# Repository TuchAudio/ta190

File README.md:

# ta190
Low Noise Moving-Coil Pre-Amplifier

## Purpose
Generic _standalone_ pre-preamp for **Moving Coil** phono cartridges, applying a fixed linear voltage gain.

## Design
The use of **four _common-base_ stages in parallel**  provides **low input impedance** (100 Ω) and **improved _signal-to-noise_ ratio** (by 6 dB).

## Specs
- **Power supply:** 9-12 V, asymmetrical (just a few mA)
- **Gain:** x33 (+34 dB)
- **Input Sensitivity:** 0.11 mV over 100 Ω (for a 3.6 mV output, suitable for [TuchAudio 103 preamp](../../../ta103))
- **Nominal Output level:** 3.6 mV over 110 kΩ (from a 0.11 mV input)
- **Output impedance:** 3.3 kΩ. _Lower load impedances are allowed, but diminished output level and impaired bass response are to be expected_.

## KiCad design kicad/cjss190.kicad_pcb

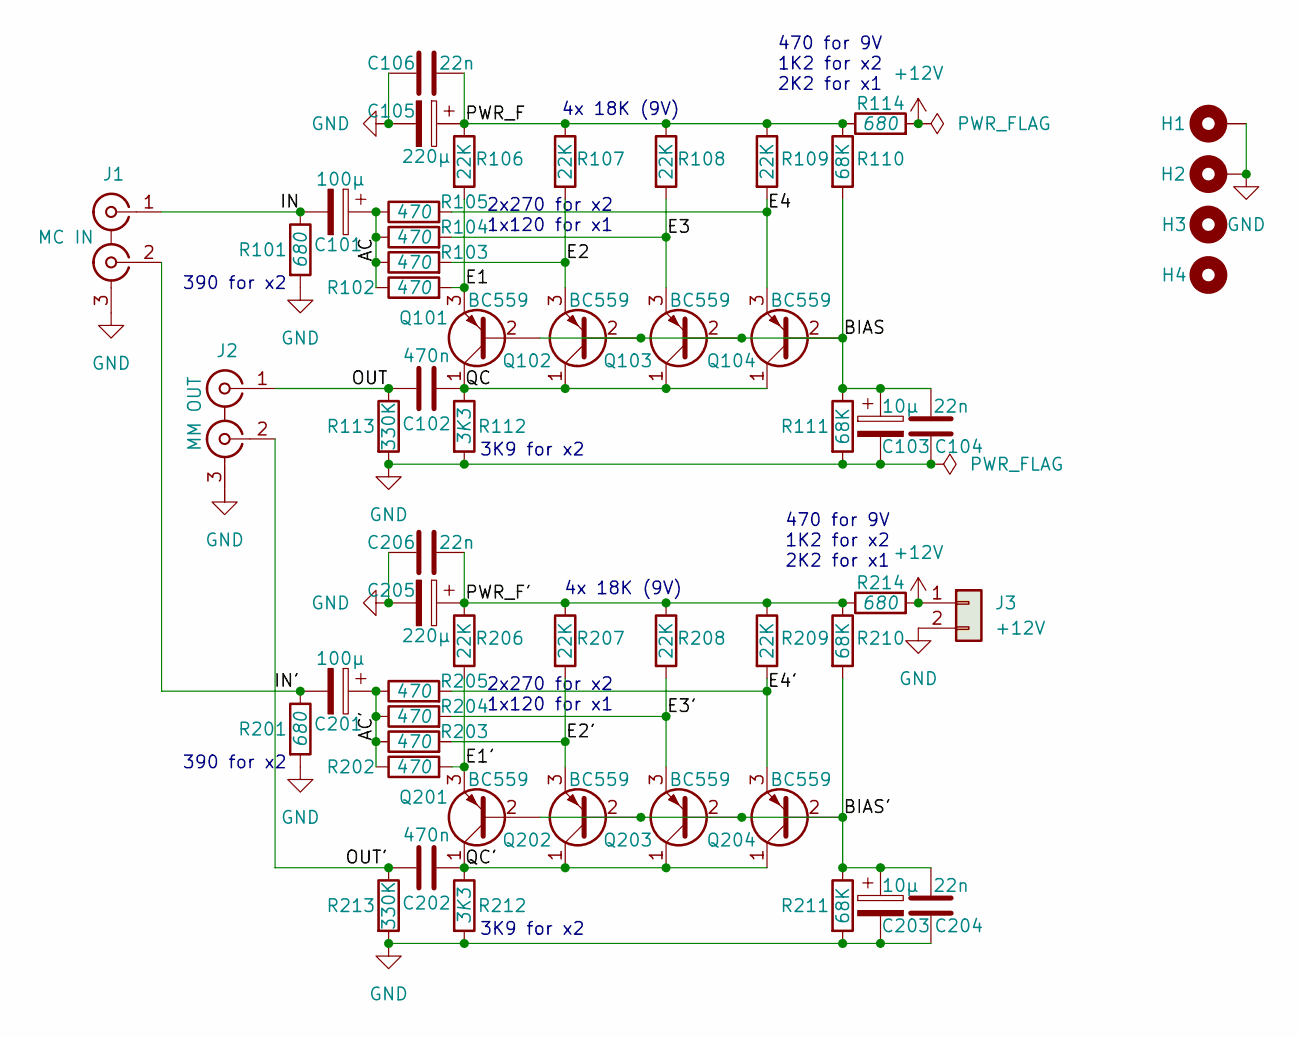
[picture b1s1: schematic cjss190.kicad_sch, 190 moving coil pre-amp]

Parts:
C101, C201: 100µ; CP_Radial_D4.0mm_P1.50mm
C102, C202: 470n; C_Rect_L7.2mm_W3.0mm_P5.00mm_FKS2_FKP2_MKS2_MKP2
C103, C203: 10µ; CP_Radial_D4.0mm_P1.50mm
C104, C106, C204, C206: 22n; C_Disc_D6.0mm_W2.5mm_P5.00mm
C105, C205: 220µ; CP_Radial_D6.3mm_P2.50mm
H1, H2: MountingHole_Pad; MountingHole_3.2mm_M3_DIN965_Pad
H3, H4: MountingHole; MountingHole_3.2mm_M3
J1: MC IN; 2xRCA_vertical
J2: MM OUT; 2xRCA_vertical
J3: +12V; PinSocket_1x02_P2.54mm_Vertical
Q101, Q102, Q103, Q104, Q201, Q202, Q203, Q204: BC559; TO-92_Inline
R101, R114, R201, R214: 680; R_Axial_DIN0207_L6.3mm_D2.5mm_P10.16mm_Horizontal
R102, R103, R104, R105, R202, R203, R204, R205: 470; R_Axial_DIN0207_L6.3mm_D2.5mm_P10.16mm_Horizontal
R106, R107, R108, R109, R206, R207, R208, R209: 22K; R_Axial_DIN0207_L6.3mm_D2.5mm_P10.16mm_Horizontal
R110, R111, R210, R211: 68K; R_Axial_DIN0207_L6.3mm_D2.5mm_P10.16mm_Horizontal
R112, R212: 3K3; R_Axial_DIN0207_L6.3mm_D2.5mm_P10.16mm_Horizontal
R113, R213: 330K; R_Axial_DIN0207_L6.3mm_D2.5mm_P10.16mm_Horizontal

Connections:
+12V: J3.1, R114.2, R214.2
/AC: C101.1, R102.1, R103.1, R104.1, R105.1
/AC': C201.1, R202.1, R203.1, R204.1, R205.1
/BIAS: C103.1, C104.1, Q101.2 (B), Q102.2 (B), Q103.2 (B), Q104.2 (B), R110.2, R111.1
/BIAS': C203.1, C204.1, Q201.2 (B), Q202.2 (B), Q203.2 (B), Q204.2 (B), R210.2, R211.1
/E1: Q101.3 (E), R102.2, R106.2
/E1': Q201.3 (E), R202.2, R206.2
/E2: Q102.3 (E), R103.2, R107.2
/E2': Q202.3 (E), R203.2, R207.2
/E3: Q103.3 (E), R104.2, R108.2
/E3': Q203.3 (E), R204.2, R208.2
/E4: Q104.3 (E), R105.2, R109.2
/E4': Q204.3 (E), R205.2, R209.2
/IN: C101.2, J1.1 (IN1), R101.1
/IN': C201.2, J1.2 (IN2), R201.1
/OUT: C102.1, J2.1 (IN1), R113.1
/OUT': C202.1, J2.2 (IN2), R213.1
/PWR_F: C105.1, C106.2, R106.1, R107.1, R108.1, R109.1, R110.1, R114.1
/PWR_F': C205.1, C206.2, R206.1, R207.1, R208.1, R209.1, R210.1, R214.1
/QC: C102.2, Q101.1 (C), Q102.1 (C), Q103.1 (C), Q104.1 (C), R112.1
/QC': C202.2, Q201.1 (C), Q202.1 (C), Q203.1 (C), Q204.1 (C), R212.1
GND: C103.2, C104.2, C105.2, C106.1, C203.2, C204.2, C205.2, C206.1, H1.1, H2.1, J1.3 (EXT), J2.3 (EXT), J3.2, R101.2, R111.2, R112.2, R113.2, R201.2, R211.2, R212.2, R213.2

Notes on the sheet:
470 for 9V 1K2 for x2 2K2 for x1
390 for x2
3K9 for x2
4x 18K (9V)
2x270 for x2 1x120 for x1

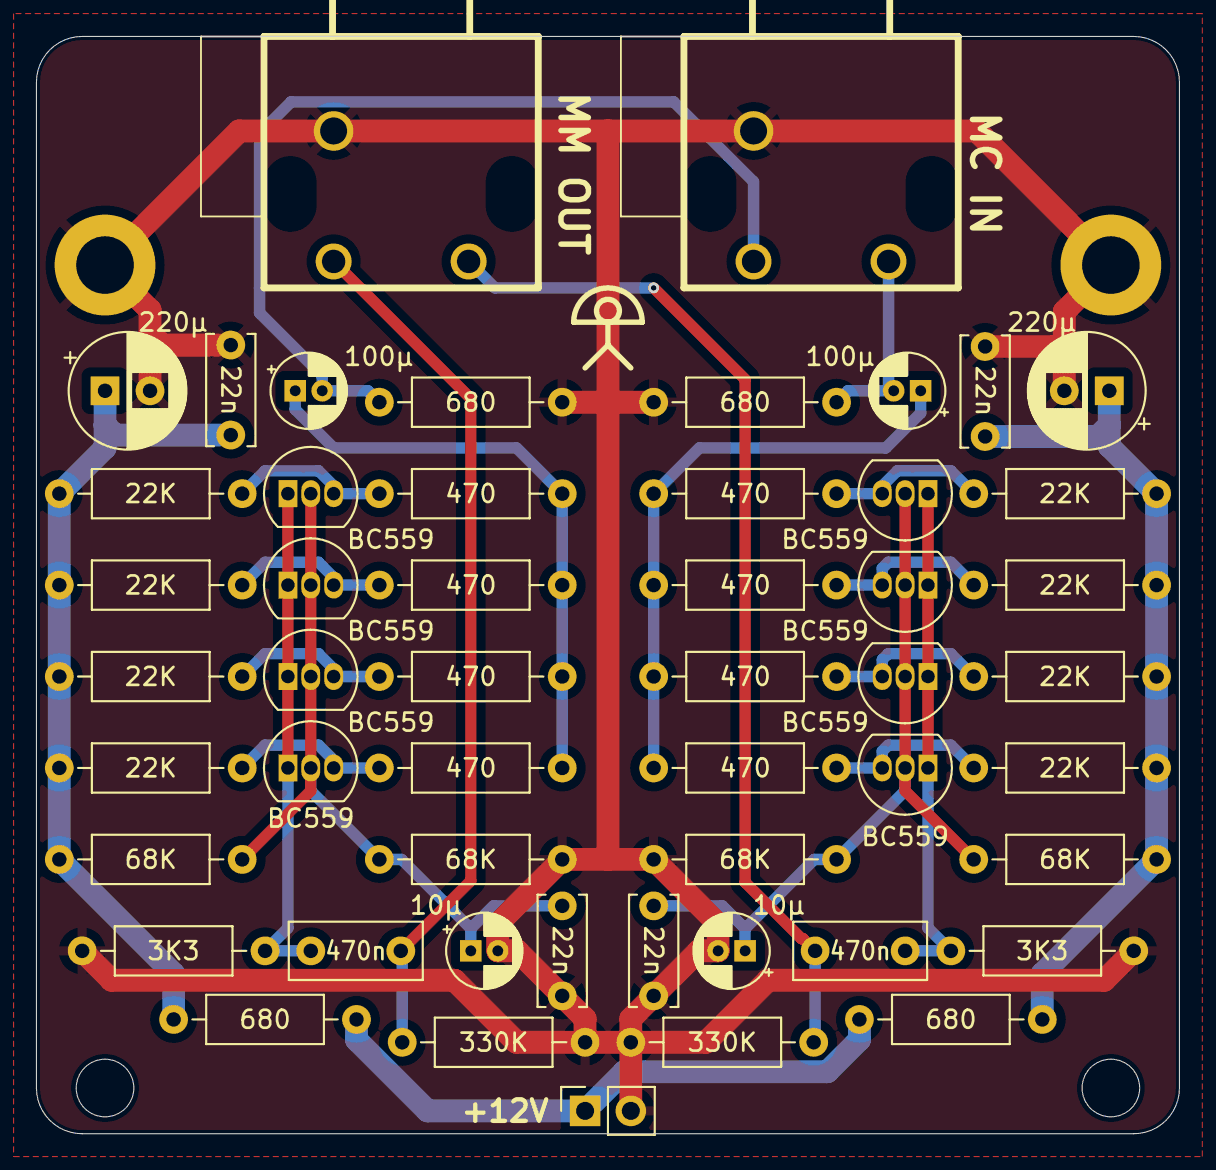
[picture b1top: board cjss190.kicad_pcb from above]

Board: 2 copper layers, 63.5 x 61.0 mm, 55 parts (0 on the bottom side), 22 nets.

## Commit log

2025-11-08 add KiCAD files
2025-11-12 Basic specs
2025-11-12 add pics
